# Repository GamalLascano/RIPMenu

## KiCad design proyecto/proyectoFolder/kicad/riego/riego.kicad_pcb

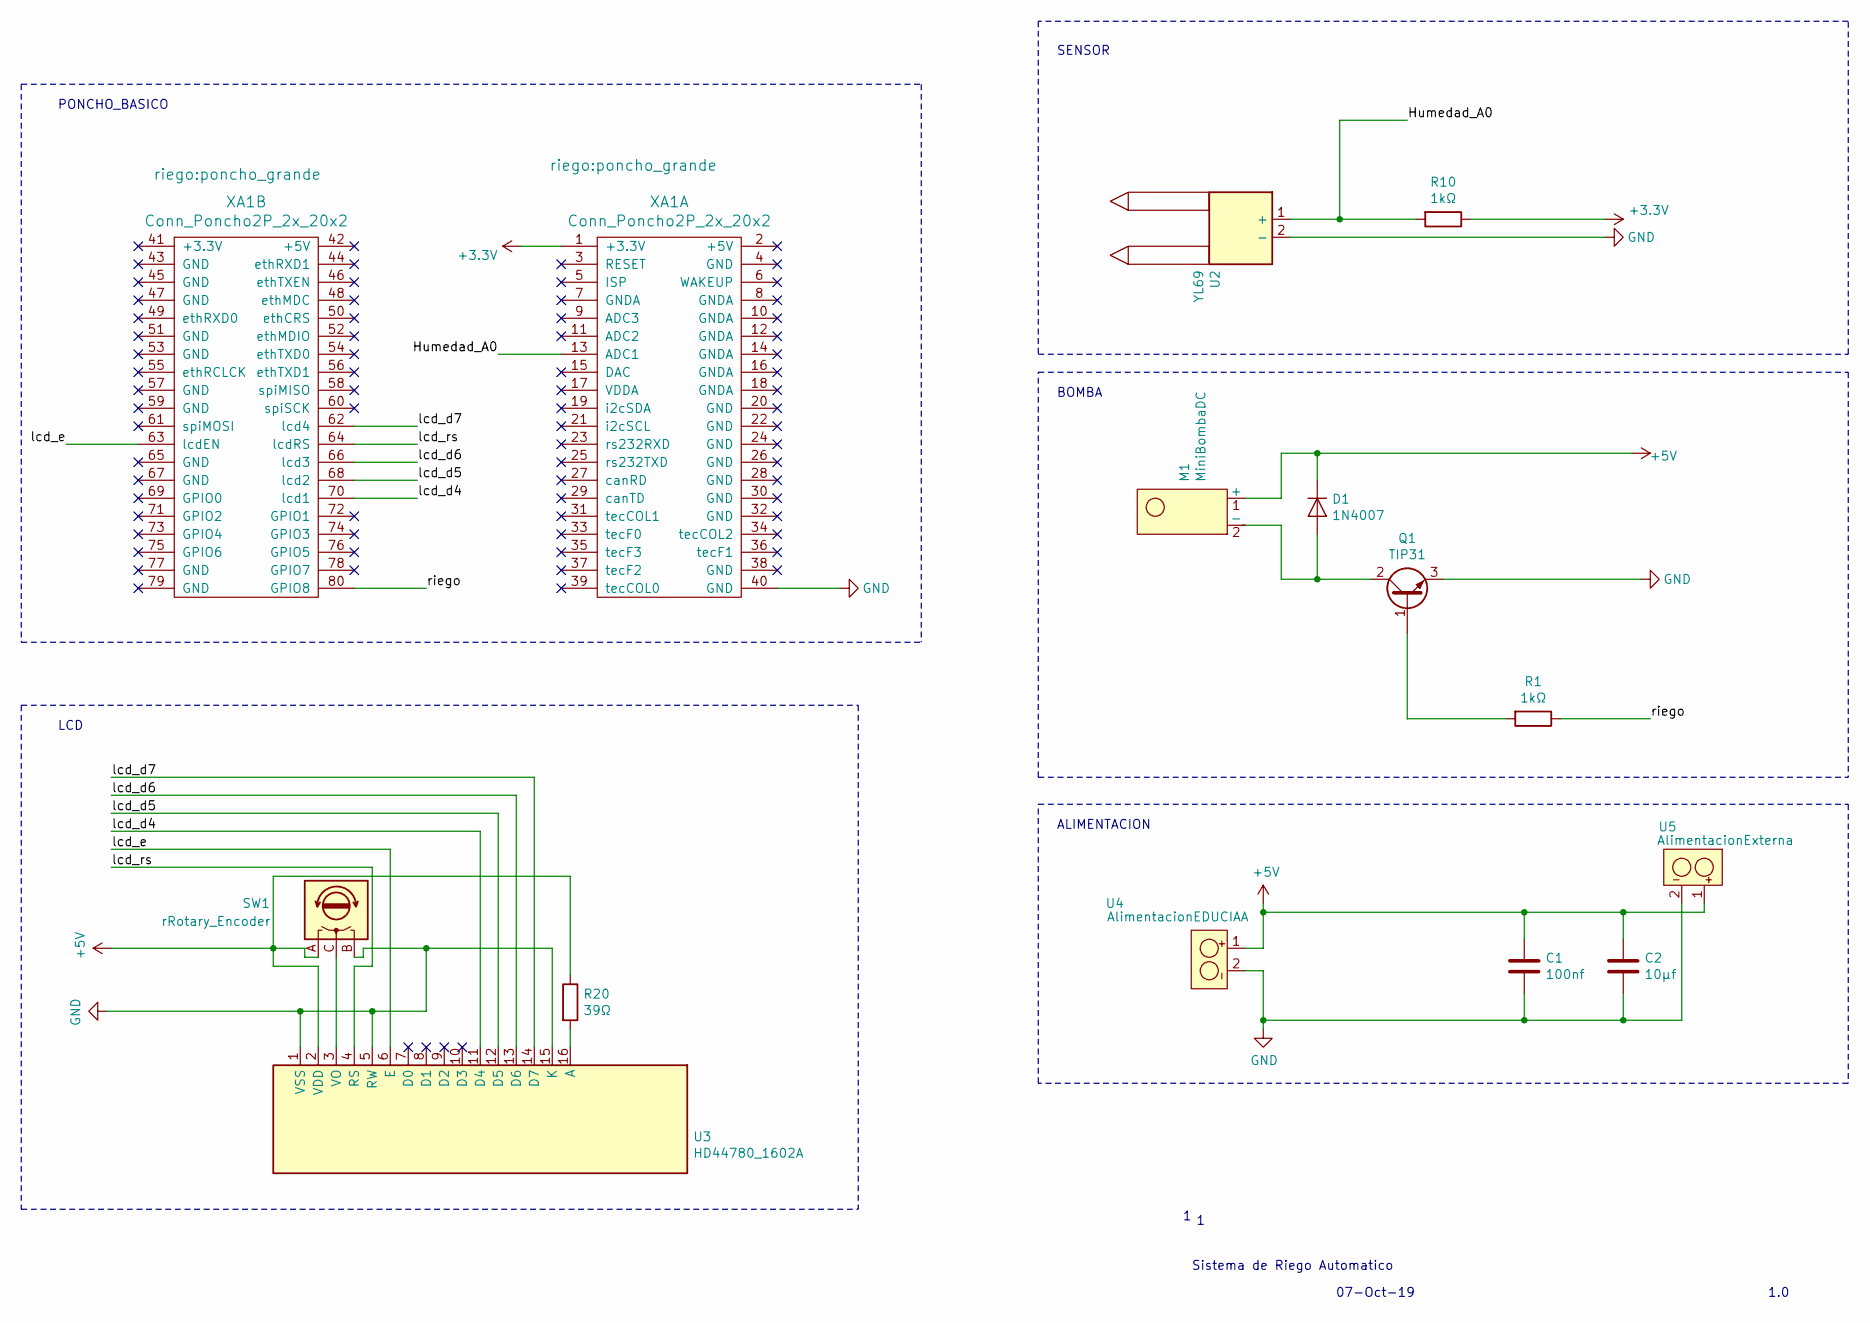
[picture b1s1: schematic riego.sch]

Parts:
C1: 100nf; C_Disc_D3.0mm_W1.6mm_P2.50mm
C2: 10μf; CP_Radial_D4.0mm_P2.00mm
D1: 1N4007; D_DO-41_SOD81_P10.16mm_Horizontal
M1: MiniBombaDC; PinSocket_1x02_P2.54mm_Vertical
Q1: TIP31; TO-220-3_Vertical
R1, R10: 1kΩ; R_Axial_DIN0207_L6.3mm_D2.5mm_P10.16mm_Horizontal
R20: 39Ω; R_Axial_DIN0207_L6.3mm_D2.5mm_P10.16mm_Horizontal
SW1: rRotary_Encoder; rPotentiometer
U2: YL69; PinSocket_1x02_P2.54mm_Vertical
U3: HD44780_1602A; rLCD16x2
U4: AlimentacionEDUCIAA; PinHeader_1x02_P2.54mm_Vertical
U5: AlimentacionExterna; PinHeader_1x02_P2.54mm_Vertical
XA1: Conn_Poncho2P_2x_20x2; poncho_grande

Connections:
+3V3: R10.1, XA1.1 (+3.3V)
+5V: C1.1, C2.1, D1.1 (K), M1.1 (+), R20.1, SW1.A, U3.2 (VDD), U4.1, U5.1
/Humedad_A0: R10.2, U2.1 (+), XA1.13 (ADC1)
/lcd_d4: U3.11 (D4), XA1.70 (lcd1)
/lcd_d5: U3.12 (D5), XA1.68 (lcd2)
/lcd_d6: U3.13 (D6), XA1.66 (lcd3)
/lcd_d7: U3.14 (D7), XA1.62 (lcd4)
/lcd_e: U3.6 (E), XA1.63 (lcdEN)
/lcd_rs: U3.4 (RS), XA1.64 (lcdRS)
/riego: R1.1, XA1.80 (GPIO8)
GND: C1.2, C2.2, Q1.3 (E), SW1.B, U2.2 (-), U3.1 (VSS), U3.5 (RW), U3.15 (K), U4.2, U5.2, XA1.40 (GND)
unnamed: D1.2 (A), M1.2 (-), Q1.2 (C)
unnamed: Q1.1 (B), R1.2
unnamed: R20.2, U3.16 (A)
unnamed: SW1.C, U3.3 (VO)

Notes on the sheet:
Sistema de Riego Automatico
07-Oct-19
1.0
LCD
PONCHO_BASICO
BOMBA
SENSOR
ALIMENTACION

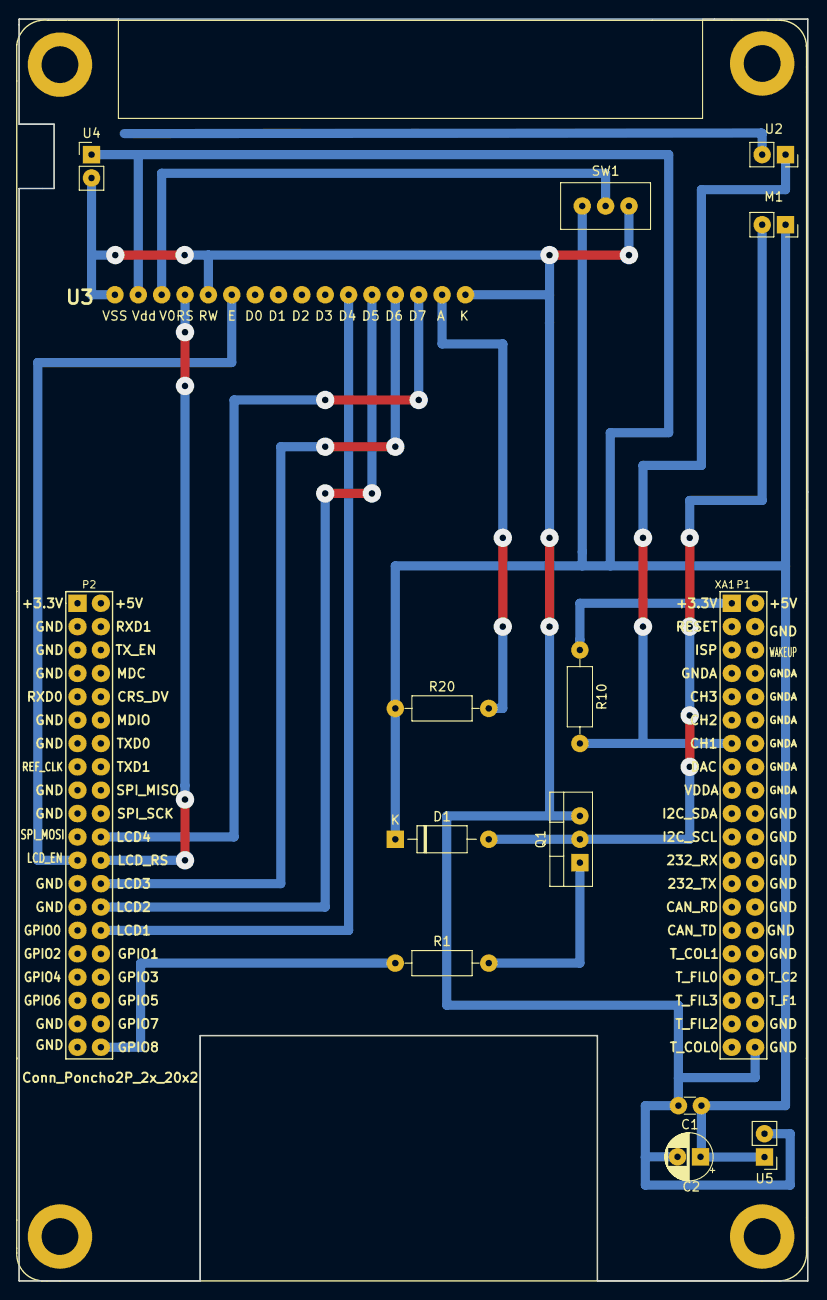
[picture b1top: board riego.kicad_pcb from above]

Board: 2 copper layers, 85.7 x 137.2 mm, 14 parts (0 on the bottom side), 15 nets.

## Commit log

2019-11-19 First try
2019-11-19 Smol
2019-11-19 ClockOSD changes
2019-11-19 Rebuilt Menu
2019-11-19 Re-added MenuOP
2019-11-19 Direct Scheme Done + First Beta
2019-11-20 Small fix to MEF
2019-11-20 First test
2019-11-20 Everything is working again
2019-11-20 Small tweaks
2019-11-21 Starting with humeManager
2019-11-21 Smol fix to OSD
2019-11-21 +1 file
2019-11-21 Added humidity changes
2019-11-25 Started with Automatic function
2019-11-25 Added direct functionality
2019-11-25 Fixed bugs
2019-11-26 Started work on auto mode
2019-11-30 Deleted useless lines
2019-12-02 Kicad files
2019-12-05 Direct working
2019-12-05 Clock partially working (needs testing)
2019-12-09 Added auto + fixed some timer stuff (?)
2019-12-09 Extra stuff
2019-12-09 Reorganized file struct + deleted libraries
2019-12-11 Finished Project
2019-12-11 Fixed grammar
2019-12-13 Calibrated sensor
2019-12-14 Final touches
2019-12-16 Changed Direct Behaviour
